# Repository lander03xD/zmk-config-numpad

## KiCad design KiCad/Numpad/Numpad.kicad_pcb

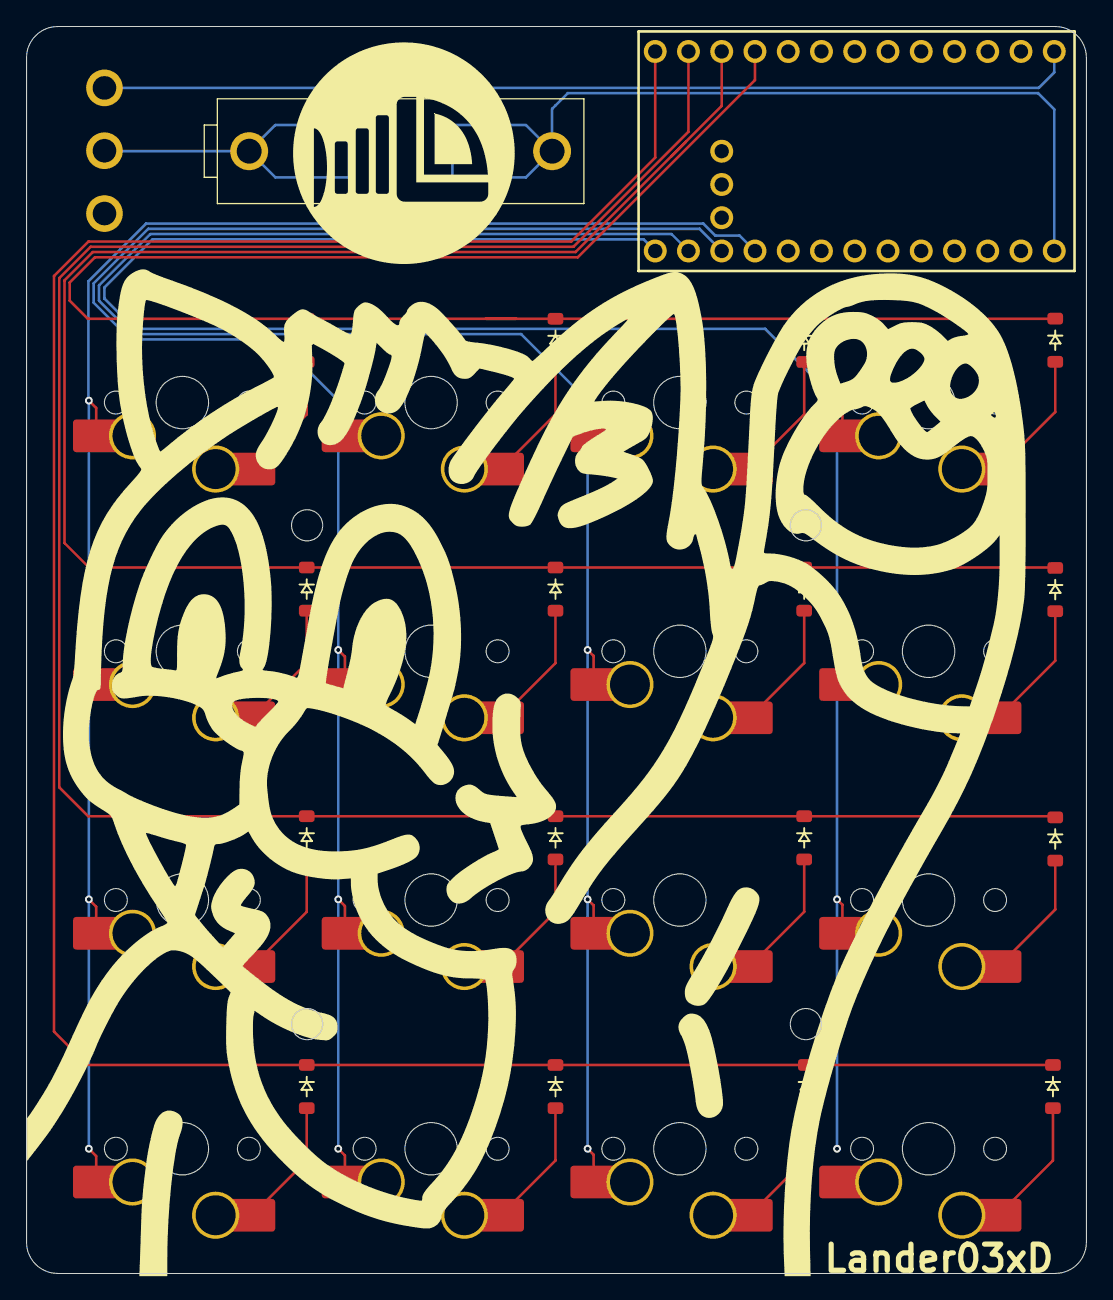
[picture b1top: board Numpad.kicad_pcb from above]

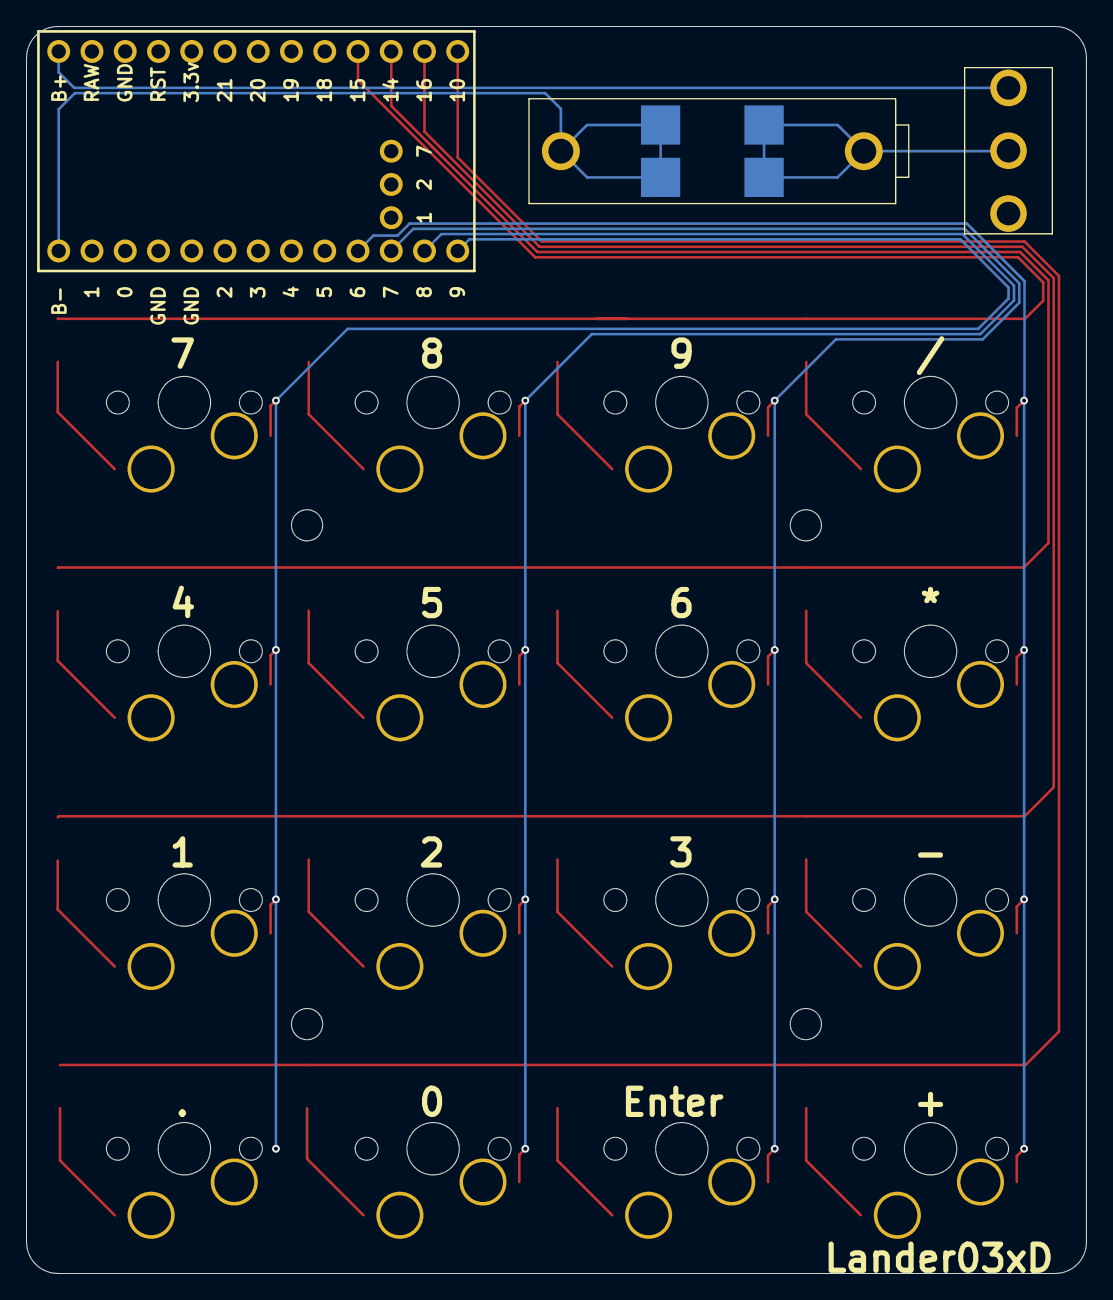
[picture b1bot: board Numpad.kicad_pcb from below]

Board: 2 copper layers, 81.0 x 95.3 mm, 35 parts (3 on the bottom side), 27 nets.

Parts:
BT1: Battery_Cell; SbM-9202_14250_battery_holder
D1, D2, D3, D4, D5, D6, D7, D8, D9, D10, D11, D12, D13, D14, D15, D16: Diode; Diode_SOD-123
S1, S2, S3, S4, S5, S6, S7, S8, S9, S10, S11, S12, S13, S14, S15, S16: Keyswitch; MX_Hotswap_1.00u
SW1: SW_SPDT_312; SW_Vertical_Slide_5mm
U1: Promicro_NRF52840; Promicro_nrf52840

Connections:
B+: SW1.3 (A), U1.28 (B+)
B-: BT1.2 (-), U1.29 (B-)
Col_1: S1.1, S4.1, S7.1, S10.1, U1.9 (6)
Col_2: S2.1, S5.1, S8.1, S11.1, U1.10 (7)
Col_3: S3.1, S6.1, S9.1, S12.1, U1.11 (8)
Col_4: S13.1, S14.1, S15.1, S16.1, U1.12 (9)
unnamed: BT1.1 (+), SW1.1 (B)
unnamed: D1.2 (A), S1.2
unnamed: D2.2 (A), S2.2
unnamed: D3.2 (A), S3.2
unnamed: D4.2 (A), S4.2
unnamed: D5.2 (A), S5.2
unnamed: D6.2 (A), S6.2
unnamed: D7.2 (A), S7.2
unnamed: D8.2 (A), S8.2
unnamed: D9.2 (A), S9.2
unnamed: D10.2 (A), S10.2
unnamed: D11.2 (A), S11.2
unnamed: D12.2 (A), S12.2
unnamed: D13.2 (A), S13.2
unnamed: D14.2 (A), S14.2
unnamed: D15.2 (A), S15.2
unnamed: D16.2 (A), S16.2
Row_1: D1.1 (K), D2.1 (K), D3.1 (K), D13.1 (K), U1.16 (15)
Row_2: D4.1 (K), D5.1 (K), D6.1 (K), D14.1 (K), U1.15 (14)
Row_3: D7.1 (K), D8.1 (K), D9.1 (K), D15.1 (K), U1.14 (16)
Row_4: D10.1 (K), D11.1 (K), D12.1 (K), D16.1 (K), U1.13 (10)

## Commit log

2025-08-03 Initial User Config.
2025-08-03 numpad files
2025-08-05 changed to the kicad files
2025-08-07 initial layout
2025-08-07 removed duplicate physical layout node
2025-08-17 correct gpio pins
2025-08-17 added numlock
2025-08-17 config layer
2025-08-20 keymap rework
2025-08-20 correct extra layer name
2025-08-23 reorder physical layout and add name
2025-08-23 add settings reset
2025-08-23 remove unused include statement
2025-08-23 added battery optimizations
